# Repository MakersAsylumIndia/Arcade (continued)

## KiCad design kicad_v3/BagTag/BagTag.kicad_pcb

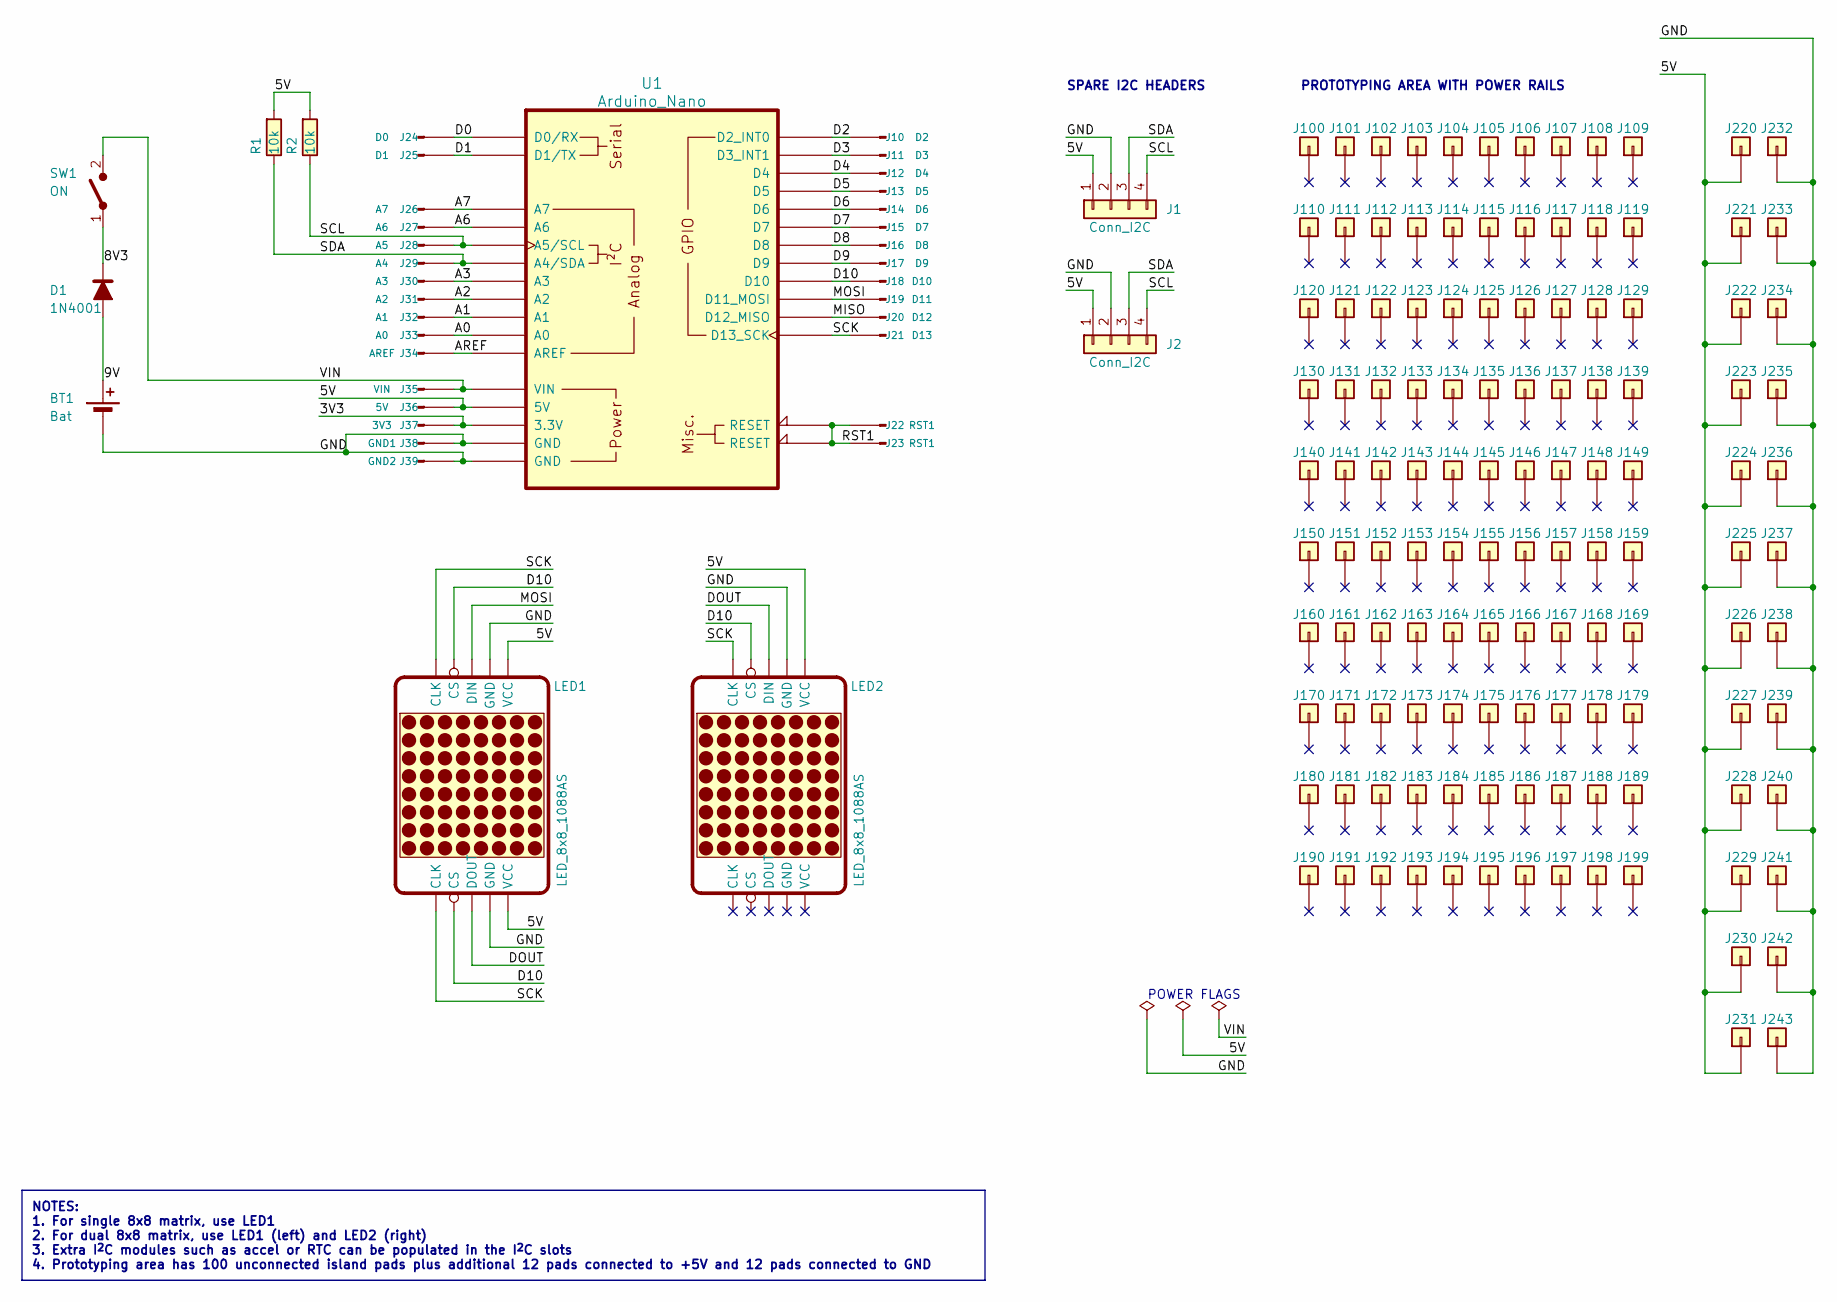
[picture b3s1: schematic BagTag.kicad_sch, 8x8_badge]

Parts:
BT1: Bat; PinHeader_1x02_P2.54mm_Vertical
D1: 1N4001; D_DO-41_SOD81_P10.16mm_Horizontal
J1, J2: Conn_I2C; PinHeader_1x04_P2.54mm_Vertical
J10: D2; PinHeader_1x01_P2.54mm_Vertical
J11: D3; PinHeader_1x01_P2.54mm_Vertical
J12: D4; PinHeader_1x01_P2.54mm_Vertical
J13: D5; PinHeader_1x01_P2.54mm_Vertical
J14: D6; PinHeader_1x01_P2.54mm_Vertical
J15: D7; PinHeader_1x01_P2.54mm_Vertical
J16: D8; PinHeader_1x01_P2.54mm_Vertical
J17: D9; PinHeader_1x01_P2.54mm_Vertical
J18: D10; PinHeader_1x01_P2.54mm_Vertical
J19: D11; PinHeader_1x01_P2.54mm_Vertical
J20: D12; PinHeader_1x01_P2.54mm_Vertical
J21: D13; PinHeader_1x01_P2.54mm_Vertical
J22, J23: RST1; PinHeader_1x01_P2.54mm_Vertical
J24: D0; PinHeader_1x01_P2.54mm_Vertical
J25: D1; PinHeader_1x01_P2.54mm_Vertical
J26: A7; PinHeader_1x01_P2.54mm_Vertical
J27: A6; PinHeader_1x01_P2.54mm_Vertical
J28: A5; PinHeader_1x01_P2.54mm_Vertical
J29: A4; PinHeader_1x01_P2.54mm_Vertical
J30: A3; PinHeader_1x01_P2.54mm_Vertical
J31: A2; PinHeader_1x01_P2.54mm_Vertical
J32: A1; PinHeader_1x01_P2.54mm_Vertical
J33: A0; PinHeader_1x01_P2.54mm_Vertical
J34: AREF; PinHeader_1x01_P2.54mm_Vertical
J35: VIN; PinHeader_1x01_P2.54mm_Vertical
J36: 5V; PinHeader_1x01_P2.54mm_Vertical
J37: 3V3; PinHeader_1x01_P2.54mm_Vertical
J38: GND1; PinHeader_1x01_P2.54mm_Vertical
J39: GND2; PinHeader_1x01_P2.54mm_Vertical
J100, J101, J102, J103, J104, J105, J106, J107, J108, J109, J110, J111, J112, J113, J114, J115, J116, J117, J118, J119, J120, J121, J122, J123, J124, J125, J126, J127, J128, J129, J130, J131, J132, J133, J134, J135, J136, J137, J138, J139, J140, J141, J142, J143, J144, J145, J146, J147, J148, J149, J150, J151, J152, J153, J154, J155, J156, J157, J158, J159, J160, J161, J162, J163, J164, J165, J166, J167, J168, J169, J170, J171, J172, J173, J174, J175, J176, J177, J178, J179, J180, J181, J182, J183, J184, J185, J186, J187, J188, J189, J190, J191, J192, J193, J194, J195, J196, J197, J198, J199, J220, J221, J222, J223, J224, J225, J226, J227, J228, J229, J230, J231, J232, J233, J234, J235, J236, J237, J238, J239, J240, J241, J242, J243: Conn_01x01; PinHeader_1x01_P2.54mm_Vertical
LED1: LED_8x8_1088AS; LED_matrix_8x8_M1088ASR
LED2: LED_8x8_1088AS; LED_matrix_8x8_M1088ASR_half
R1, R2: 10k; R_Axial_DIN0207_L6.3mm_D2.5mm_P7.62mm_Horizontal
SW1: ON; SW_CuK_OS102011MA1QN1_SPDT_Angled
U1: Arduino_Nano; Arduino_Nano_v2_NoSPI

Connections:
/3V3: J37.1, U1.3V3 (3.3V)
/5V: J1.1, J2.1, J36.1, J220.1, J221.1, J222.1, J223.1, J224.1, J225.1, J226.1, J227.1, J228.1, J229.1, J230.1, J231.1, LED1.VCC, LED2.VCC, R1.1, R2.1, U1.5V
/8V3: D1.1 (K), SW1.1 (A)
/9V: BT1.1 (+), D1.2 (A)
/A0: J33.1, U1.A0
/A1: J32.1, U1.A1
/A2: J31.1, U1.A2
/A3: J30.1, U1.A3
/A6: J27.1, U1.A6
/A7: J26.1, U1.A7
/AREF: J34.1, U1.AREF
/D0: J24.1, U1.D0 (D0/RX)
/D1: J25.1, U1.D1 (D1/TX)
/D2: J10.1, U1.D2 (D2_INT0)
/D3: J11.1, U1.D3 (D3_INT1)
/D4: J12.1, U1.D4
/D5: J13.1, U1.D5
/D6: J14.1, U1.D6
/D7: J15.1, U1.D7
/D8: J16.1, U1.D8
/D9: J17.1, U1.D9
/D10: J18.1, LED1.CS, LED2.CS, U1.D10
/DOUT: LED1.DOUT, LED2.DIN
/GND: BT1.2 (-), J1.2, J2.2, J38.1, J39.1, J232.1, J233.1, J234.1, J235.1, J236.1, J237.1, J238.1, J239.1, J240.1, J241.1, J242.1, J243.1, LED1.GND, LED2.GND, U1.GND1 (GND), U1.GND2 (GND)
/MISO: J20.1, U1.D12 (D12_MISO)
/MOSI: J19.1, LED1.DIN, U1.D11 (D11_MOSI)
/RST1: J22.1, J23.1, U1.RST1 (RESET), U1.RST2 (RESET)
/SCK: J21.1, LED1.CLK, LED2.CLK, U1.D13 (D13_SCK)
/SCL: J1.4, J2.4, J28.1, R2.2, U1.A5 (A5/SCL)
/SDA: J1.3, J2.3, J29.1, R1.2, U1.A4 (A4/SDA)
/VIN: J35.1, SW1.2 (B), U1.VIN

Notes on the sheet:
PROTOTYPING AREA WITH POWER RAILS
SPARE I2C HEADERS
POWER FLAGS
NOTES: 1. For single 8x8 matrix, use LED1 2. For dual 8x8 matrix, use LED1 (left) and LED2 (right) 3. Extra I^{2}C modules such as accel or RTC can be populated in the I^{2}C slots 4. Prototyping area has 100 unconnected island pads plus additional 12 pads connected to +5V and 12 pads connected to 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

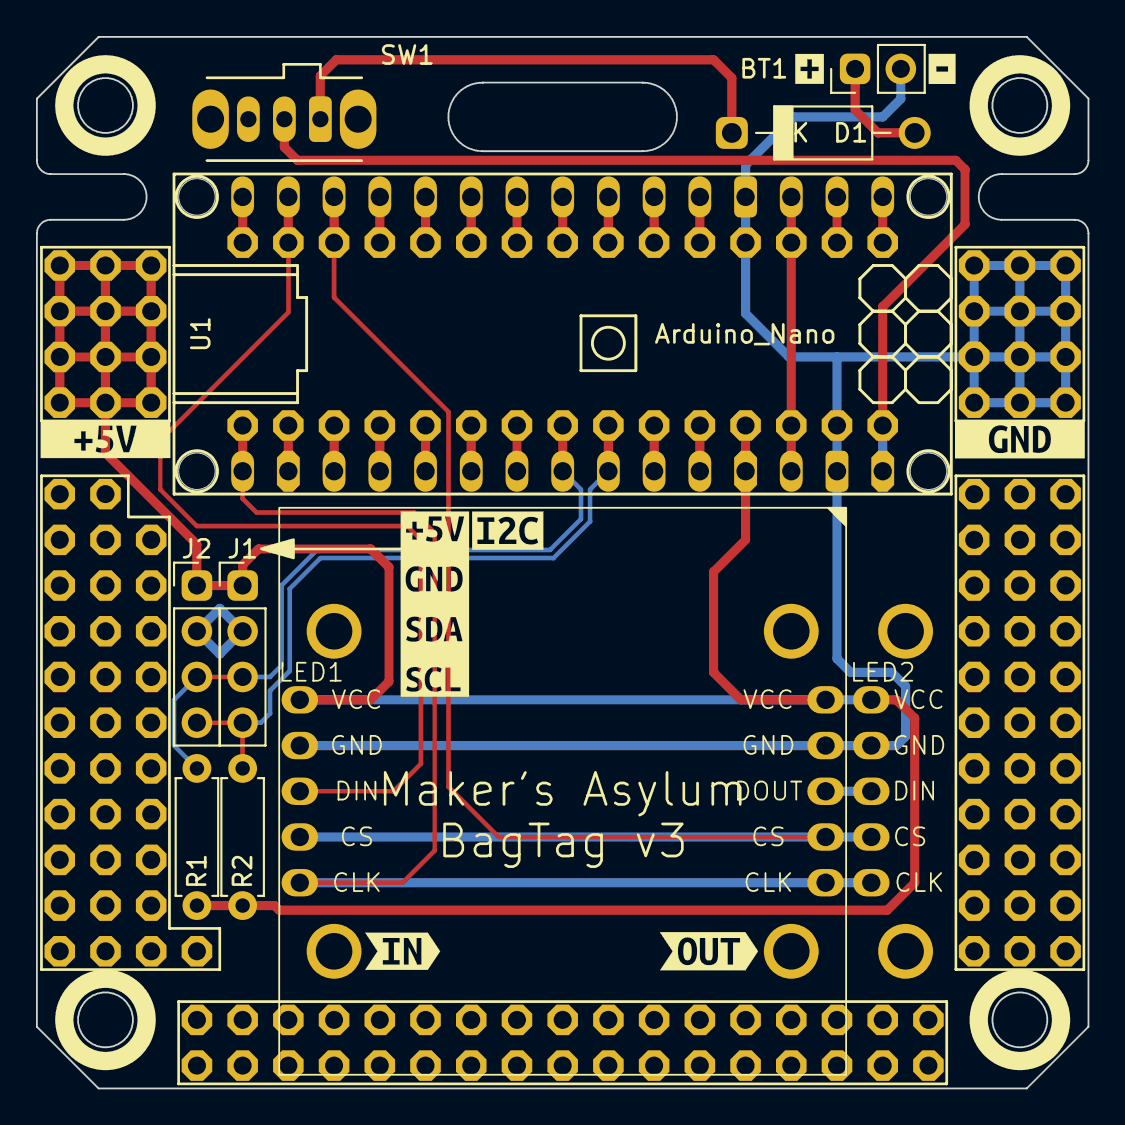
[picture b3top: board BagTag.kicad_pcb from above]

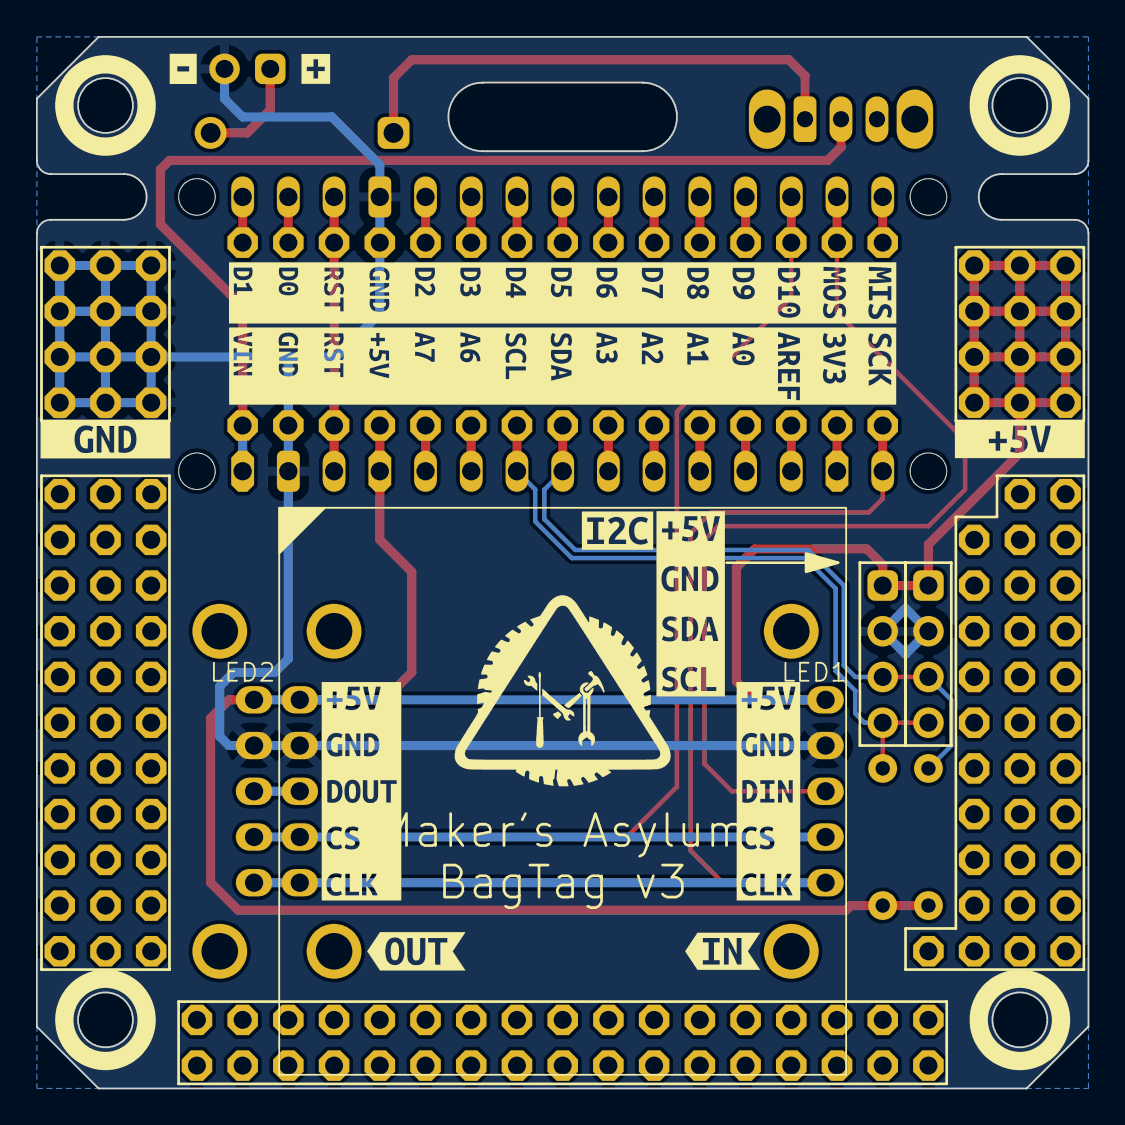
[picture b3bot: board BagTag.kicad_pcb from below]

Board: 2 copper layers, 58.4 x 58.4 mm, 184 parts (42 on the bottom side), 31 nets.

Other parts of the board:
kibuzzard-6461C6D4, kibuzzard-6461C6D4#2: G***; kibuzzard-6461C6D4
kibuzzard-6461C7CD: G***; kibuzzard-6461C7CD
kibuzzard-6461C7E5: G***; kibuzzard-6461C7E5
kibuzzard-6461CA3D: G***; kibuzzard-6461CA3D
kibuzzard-6461CA4A: G***; kibuzzard-6461CA4A
kibuzzard-6461CA6F: G***; kibuzzard-6461CA6F
kibuzzard-6461CA30: G***; kibuzzard-6461CA30
kibuzzard-6461CA59: G***; kibuzzard-6461CA59
kibuzzard-6461CA60: G***; kibuzzard-6461CA60
kibuzzard-64612FA6, kibuzzard-64612FA6#2: G***; kibuzzard-64612FA6
kibuzzard-64612FED, kibuzzard-64612FED#2: G***; kibuzzard-64612FED
kibuzzard-646132D7, kibuzzard-646132D7#2: G***; kibuzzard-646132D7
kibuzzard-646134AD: G***; kibuzzard-646134AD
kibuzzard-646134FF: G***; kibuzzard-646134FF
kibuzzard-6461376B: G***; kibuzzard-6461376B
kibuzzard-6461377A: G***; kibuzzard-6461377A

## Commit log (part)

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2023-04-18 initial commit for BagTag
2023-06-06 added v3 files
2023-06-07 updated CAD in /fabricate folder
2023-06-07 minor edit in documentation
2023-06-19 added final v3 assets including Gerbers
2023-07-14 added BagTag lasercut enclosure DXF
2023-07-21 modified DXF outputs after PCB edits
2024-05-09 ver 4 WIP - removed prototyping pads, added digital, analog and PWM headers
2024-05-13 ver 4 WIP - gerbers are ready
2024-09-04 TheThing v1 PCB and Arcade WIP
2024-09-04 Arcade update
2024-09-06 TheThing Arcade WIP
2024-09-07 TheThing Arcade WIP 2
2024-11-12 arcade enclosure ver3
2024-12-13 added hole for reset button
2024-12-15 cleanup
2025-02-07 PCB addon board and new enclosure
2025-05-09 v7 files for PCB and enclosure
2025-05-12 v7 prototype files for PCB and enclosure
2025-05-13 side retaining clips made 0.4mm smaller
2025-05-16 fixed default OLED jumper connections
2025-07-18 modified enclosure v8
2025-10-11 enclosure WIP for v8
2025-10-13 v8 enclosure final
2025-10-16 added haptic motor code
2025-10-18 codes folder reorganized
2025-10-20 codes WIP
2025-10-23 codes_testing is the folder with functional codes. code_archive is old code
2025-10-31 added revised version of pot knob
2025-11-04 v8 laser DXF for production
